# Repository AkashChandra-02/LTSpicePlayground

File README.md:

# LTSpicePlayground
A repo for me to store my spice experiments

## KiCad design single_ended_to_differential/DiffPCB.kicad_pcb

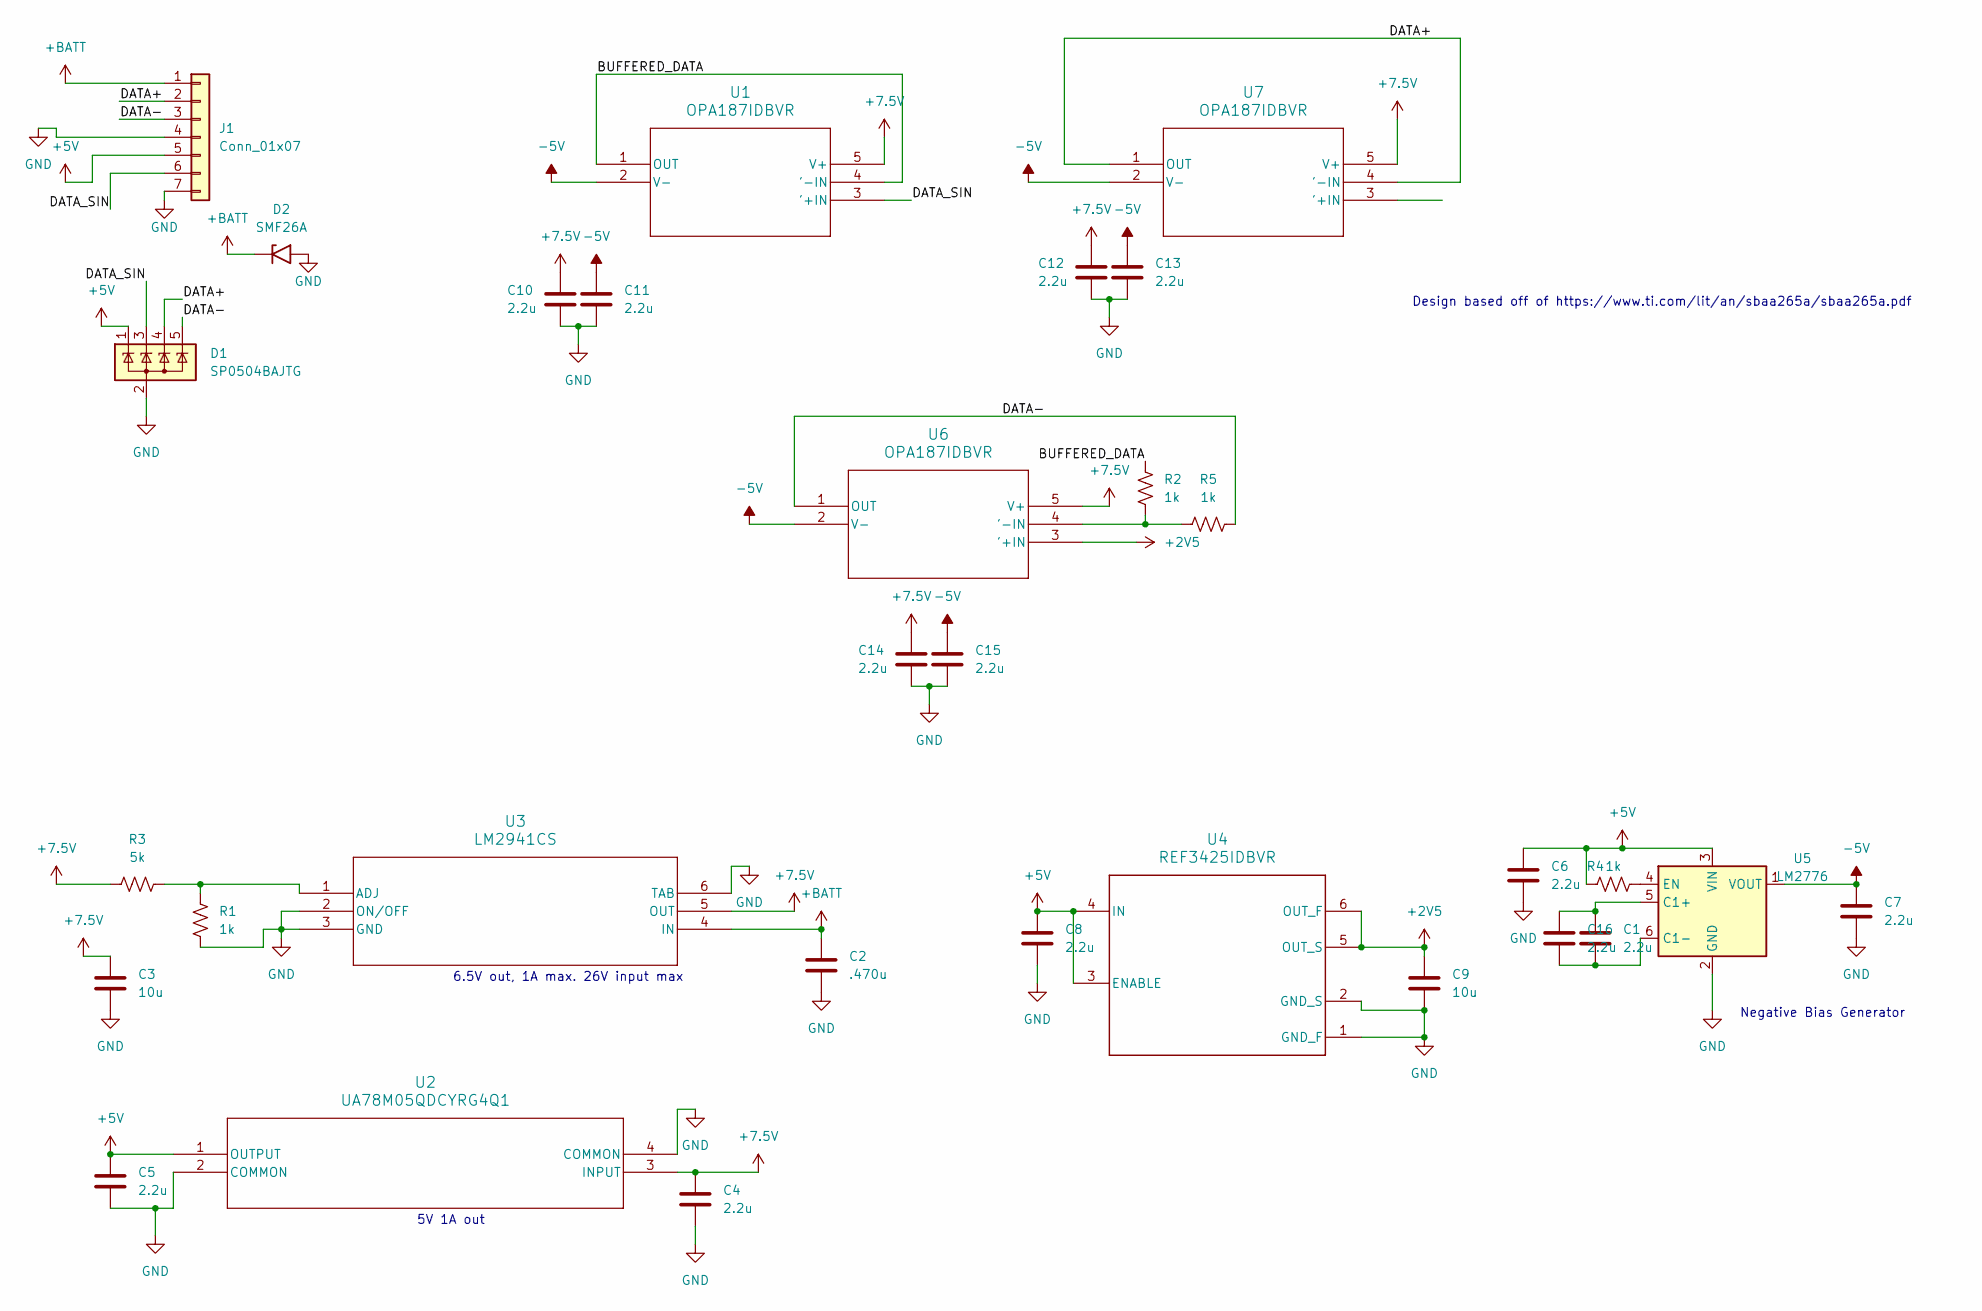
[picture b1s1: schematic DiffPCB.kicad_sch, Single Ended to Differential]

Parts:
C1, C4, C5, C6, C7, C8, C10, C11, C12, C13, C14, C15, C16: 2.2u; C_0603_1608Metric
C2: .470u; C_0603_1608Metric
C3, C9: 10u; C_0603_1608Metric
D1: SP0504BAJTG; SOT-353_SC-70-5
D2: SMF26A; D_SMF
J1: Conn_01x07; Molex_CLIK-Mate_502386-0770_1x07-1MP_P1.25mm_Horizontal
R1, R2, R4, R5: 1k; R_0603_1608Metric
R3: 5k; R_0603_1608Metric
U1, U6, U7: OPA187IDBVR; DBV5_TEX
U2: UA78M05QDCYRG4Q1; DCY4_TEX
U3: LM2941CS; TS5B
U4: REF3425IDBVR; DBV0006A_L
U5: LM2776; SOT-23-6

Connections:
+2V5: C9.1, U4.5 (OUT_S), U4.6 (OUT_F), U6.3 ('+IN)
+5V: C5.1, C6.1, C8.1, D1.1 (K), J1.5, R4.2, U2.1 (OUTPUT), U4.3 (ENABLE), U4.4 (IN), U5.3 (VIN)
+7.5V: C3.1, C4.1, C10.1, C12.1, C14.1, R3.1, U1.5 (V+), U2.3 (INPUT), U3.5 (OUT), U6.5 (V+), U7.5 (V+)
+BATT: C2.1, D2.1 (A1), J1.1, U3.4 (IN)
-5V: C7.1, C11.1, C13.1, C15.1, U1.2 (V-), U5.1 (VOUT), U6.2 (V-), U7.2 (V-)
/BUFFERED_DATA: R2.1, U1.1 (OUT), U1.4 ('-IN), U7.3 ('+IN)
/DATA+: D1.4 (K), J1.2, U7.1 (OUT), U7.4 ('-IN)
/DATA-: D1.5 (K), J1.3, R5.2, U6.1 (OUT)
/DATA_SIN: D1.3 (K), J1.6, U1.3 ('+IN)
GND: C2.2, C3.2, C4.2, C5.2, C6.2, C7.2, C8.2, C9.2, C10.2, C11.2, C12.2, C13.2, C14.2, C15.2, D1.2 (A), D2.2 (A2), J1.4, J1.7, R1.2, U2.2 (COMMON), U2.4 (COMMON), U3.2 (ON/OFF), U3.3 (GND), U3.6 (TAB), U4.1 (GND_F), U4.2 (GND_S), U5.2 (GND)
unnamed: R1.1, R3.2, U3.1 (ADJ)
unnamed: C1.1, C16.1, U5.5 (C1+)
unnamed: C1.2, C16.2, U5.6 (C1-)
unnamed: R4.1, U5.4 (EN)
unnamed: R2.2, R5.1, U6.4 ('-IN)

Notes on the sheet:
5V 1A out
Design based off of https://www.ti.com/lit/an/sbaa265a/sbaa265a.pdf
6.5V out, 1A max. 26V input max
Negative Bias Generator

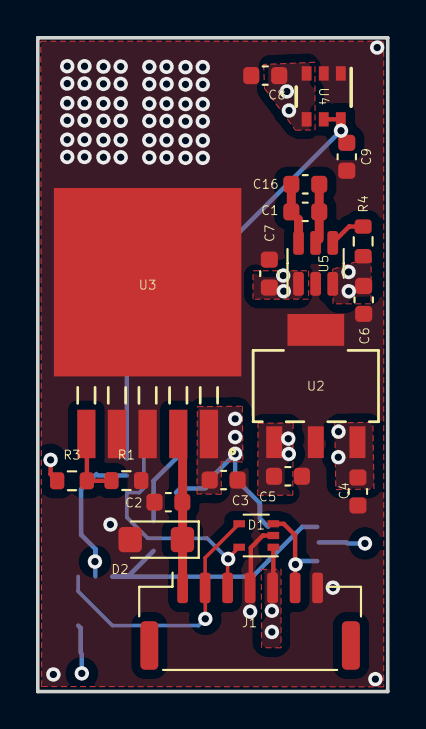
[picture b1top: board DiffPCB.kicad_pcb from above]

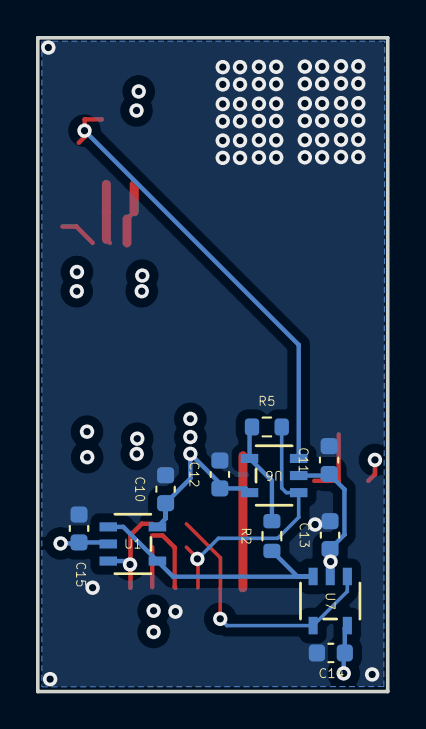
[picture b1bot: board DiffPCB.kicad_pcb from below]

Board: 6 copper layers, 19.4 x 36.3 mm, 31 parts (11 on the bottom side), 15 nets.

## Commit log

2025-10-08 adding start of 50% duty cycle 555
2025-10-09 added MVP charge pump
2025-10-09 updated git ignore
2025-10-30 added start of sims
2025-10-30 started sim and solver
2025-11-11 added more charge pump
2025-11-18 added inital design
2025-11-19 added no charge pump
2025-12-23 added single ended to diff
2025-12-23 added single ended to diff (#8)
